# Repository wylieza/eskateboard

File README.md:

## Electric Skateboard Project

Contains all the collaborative project files for Justin and Stefans
electic skateboard project.

## Versioning
### Release Version: V0.7.0
Latest Releases
  - battery container	V0.1.0
  - battery cover	V0.2.1
  - mounting plate	V0.3.0
  - bms breakout	V1.0.0
  - battery breakout    V1.0.1
  - electronics mount V1.0.0

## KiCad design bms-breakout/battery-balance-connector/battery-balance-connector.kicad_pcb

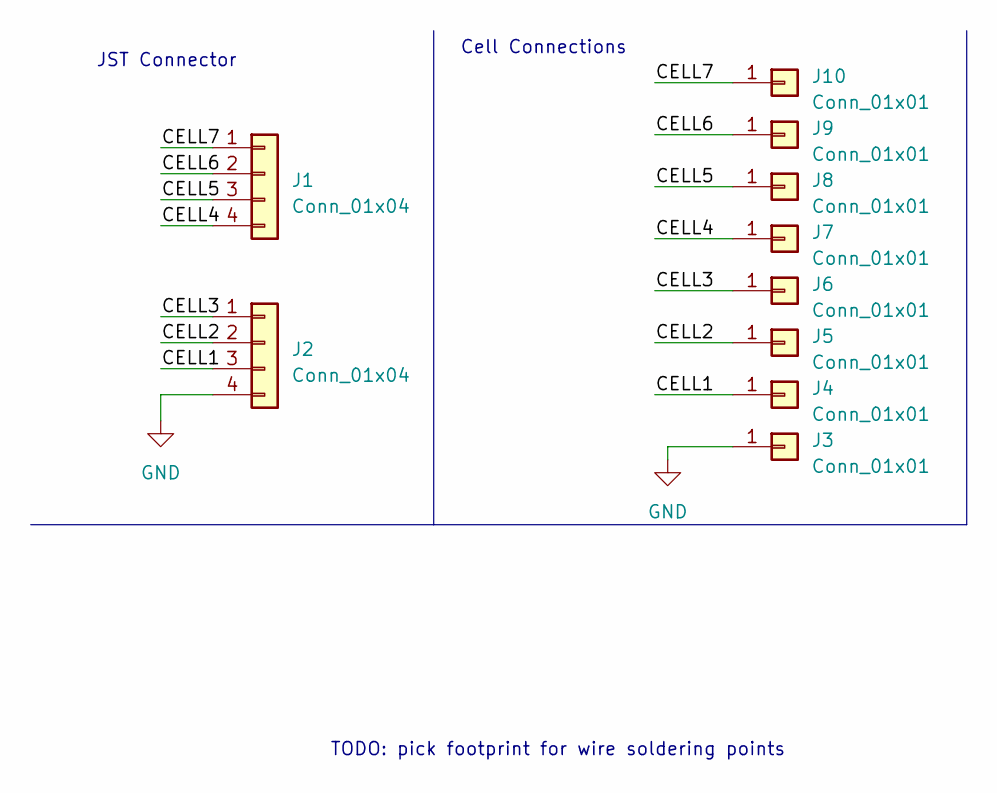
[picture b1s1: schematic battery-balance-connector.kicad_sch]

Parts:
J1, J2: Conn_01x04; JST_PH_S4B-PH-K_1x04_P2.00mm_Horizontal
J3, J4, J5, J6, J7, J8, J9, J10: Conn_01x01; SolderWirePad_1x01_SMD_2x4mm_2.7mmRelief

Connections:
/CELL1: J2.3, J4.1
/CELL2: J2.2, J5.1
/CELL3: J2.1, J6.1
/CELL4: J1.4, J7.1
/CELL5: J1.3, J8.1
/CELL6: J1.2, J9.1
/CELL7: J1.1, J10.1
GND: J2.4, J3.1

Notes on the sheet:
TODO: pick footprint for wire soldering points
Cell Connections
JST Connector

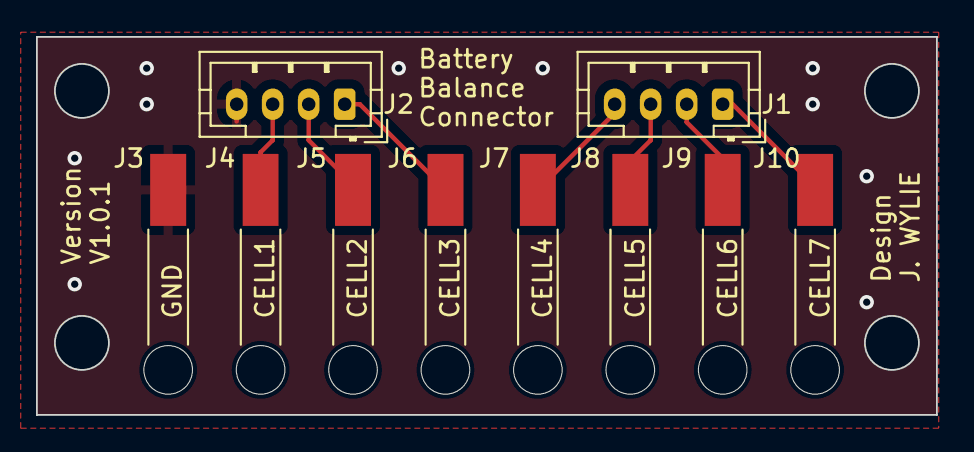
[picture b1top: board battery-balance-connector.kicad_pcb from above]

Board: 2 copper layers, 50.0 x 21.0 mm, 10 parts (0 on the bottom side), 8 nets.

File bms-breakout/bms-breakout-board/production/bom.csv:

Designator,Footprint,Quantity,Value,LCSC Part #
"J1, J2, J3, J4, J5, J6",PinHeader_1x04_P2.00mm_Horizontal,6,Conn_01x04,
J7,PinHeader_1x11_P2.54mm_Vertical,1,Conn_01x11,

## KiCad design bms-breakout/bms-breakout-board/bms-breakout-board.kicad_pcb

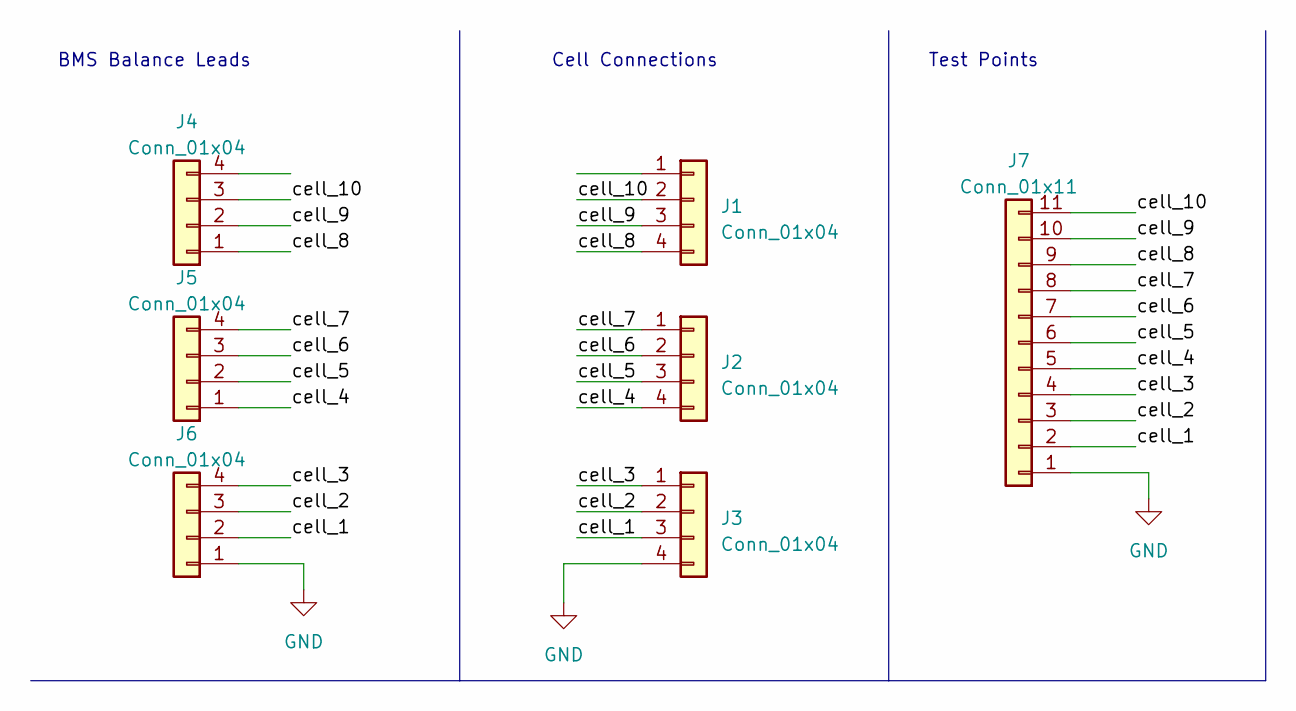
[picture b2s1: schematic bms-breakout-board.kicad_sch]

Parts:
J1, J2, J3, J4, J5, J6: Conn_01x04; PinHeader_1x04_P2.00mm_Horizontal
J7: Conn_01x11; PinHeader_1x11_P2.54mm_Vertical

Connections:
/cell_1: J3.3, J6.2, J7.2
/cell_2: J3.2, J6.3, J7.3
/cell_3: J3.1, J6.4, J7.4
/cell_4: J2.4, J5.1, J7.5
/cell_5: J2.3, J5.2, J7.6
/cell_6: J2.2, J5.3, J7.7
/cell_7: J2.1, J5.4, J7.8
/cell_8: J1.4, J4.1, J7.9
/cell_9: J1.3, J4.2, J7.10
/cell_10: J1.2, J4.3, J7.11
GND: J3.4, J6.1, J7.1

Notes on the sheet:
Test Points
Cell Connections
BMS Balance Leads

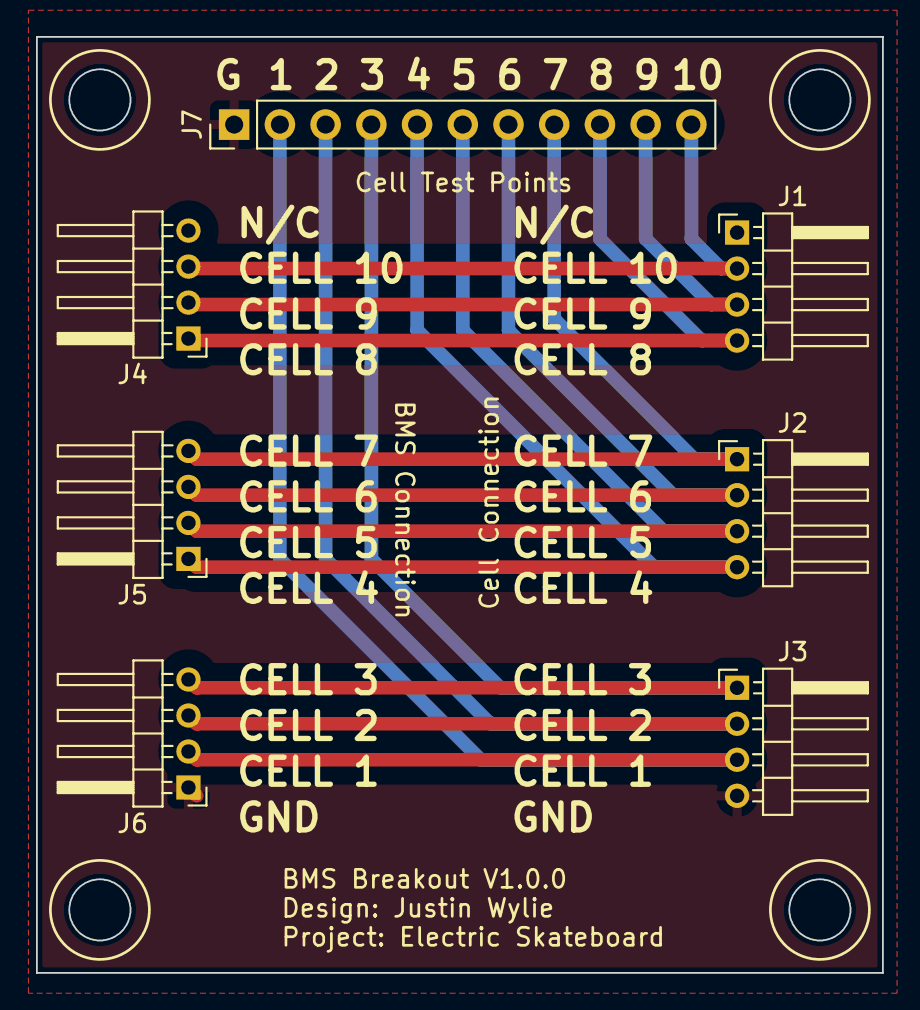
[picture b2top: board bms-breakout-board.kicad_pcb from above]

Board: 2 copper layers, 47.0 x 52.0 mm, 7 parts (0 on the bottom side), 11 nets.

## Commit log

2022-10-23 added my sketch to the repo
2022-10-24 finished piece, needing to still update mounting holes
2022-10-25 adding work so far to repo
2022-10-26 side mounting holes for box
2022-10-26 box taking shape - just need to add nuts and probably a bit of tweaking
2022-10-27 added nut insets and slots for mounting
2022-10-27 moved bolt holes so they don't go through entire shape
2022-10-27 chamfer edges
2022-10-29 using m4 nuts and bolts for mounting to plate. Added balance lead holes
2022-10-29 export to stl
2022-10-31 added tech drawing
2022-10-31 updated battery mounting hole location
2022-11-01 turned mounting hole into slot
2022-11-06 updated measurements
2022-11-06 Added fillets
2022-11-14 added tolerance to width, but not length yet because sketch breaks
2022-11-19 added 0.6mm tollerance to width and length of battery
2022-11-21 increasing tolerance futher
2023-02-21 now using versioning to keep track of things
2023-02-26 cropped print to test fit for V0.1.0
2023-02-26 created a cover for the battery box
2023-02-27 can I push to master?
2023-02-27 try with a text file
2023-02-27 I'm on the wrong branch like a tjop
2023-02-27 can I push directly to master
2023-02-27 yes I can, great
2023-02-27 added keying and made the box cover much thiner - V0.2.0
2023-02-27 fixed non-manifold issue with box cover - V0.2.1
2023-02-28 version number for plate and stl export
2023-02-28 updated for tolerances
2023-03-04 battery plate updated to V0.2.0
2023-03-04 added README with versioning info
2023-03-15 added gap for mounting holes
2023-03-16 remeasured the distance between truck holes
2023-03-16 added more fillets
2023-03-27 released mounting plate
2023-03-27 yikes
2023-05-26 begin work on the electronics mounting
2023-05-26 taking form in 3D - much tweaking ahead (and plenty more design)
2023-05-27 started work on the bms breakout
2023-05-27 cell balancing breakout board layout pretty much done
2023-05-28 finished v1.0.0 of bms breakout
2023-05-28 released V1 of the bms breakout
2023-05-28 added battery assembly docs
2023-06-03 ignore back files from kicad for bms breakout
2023-06-03 much work on the esc component of electrics mounting
2023-06-04 esc adjusted tollerances for better fit. much work on port access
2023-06-04 working on the receiver cable stow away
2023-06-05 added stow space for unused receiver cable
2023-06-05 usb port access
2023-06-08 not sure - no work done here
2023-06-08 adding cable supports for securing cable to battery box
2023-06-12 removed balance lead holes and fixed number of issues after I did that.... next I'll create slots for these leads
2023-06-21 not sure here, but files changes
2023-06-21 begin work on the front battery balance leads adapter board
2023-06-21 added backups to gitignore
2023-06-22 made some more progress on the battery balance connector
2023-06-24 V1.0.0 of battery balance connector
2023-06-24 V1.0.1 - using vertical mounting and tweaked dimensions
2023-06-24 gerbers for V1.0.1 of battery balance leads connector
2023-06-26 updated readme for release
2023-06-26 fixing up issue with some face error
2023-06-26 work on the pcb mounting and added slots for balance leads on main container
2023-07-03 finished cable support. added fillets. exported V0.3.0 stl for printing
2023-07-04 renamed to correctly identify object - not cover, but container
2023-08-07 work on the battery and the bms cable slots and fit
2023-08-09 final alignment of leads for bms before test print
2023-08-12 added a mm length and width for bms fit
2023-08-24 work on the positioning
2023-08-26 moved battery position
2023-08-26 positioning bms and battery
2023-08-26 bms balance leads
2023-08-26 trying to figure out broken battery mount
2023-08-26 calling it for now! will fix this battery issue later
2023-09-02 finally figured out the issue with that battery section! flipping from bottom to top view was confusing me
2023-09-03 accounting for balance lead going over top of battery
2023-09-03 added mounting pillars - checkpoint before smoothing edges etc.
2023-09-03 adding tons of fillets
2023-09-11 releasing V0.7.0 with completed electronics mount
2023-09-11 created V0.1.0 of the receiver and balance lead breakout mount
2023-09-13 corrected height of receiver encasing
2024-06-23 improved supporot for battery on electronics mount for board
